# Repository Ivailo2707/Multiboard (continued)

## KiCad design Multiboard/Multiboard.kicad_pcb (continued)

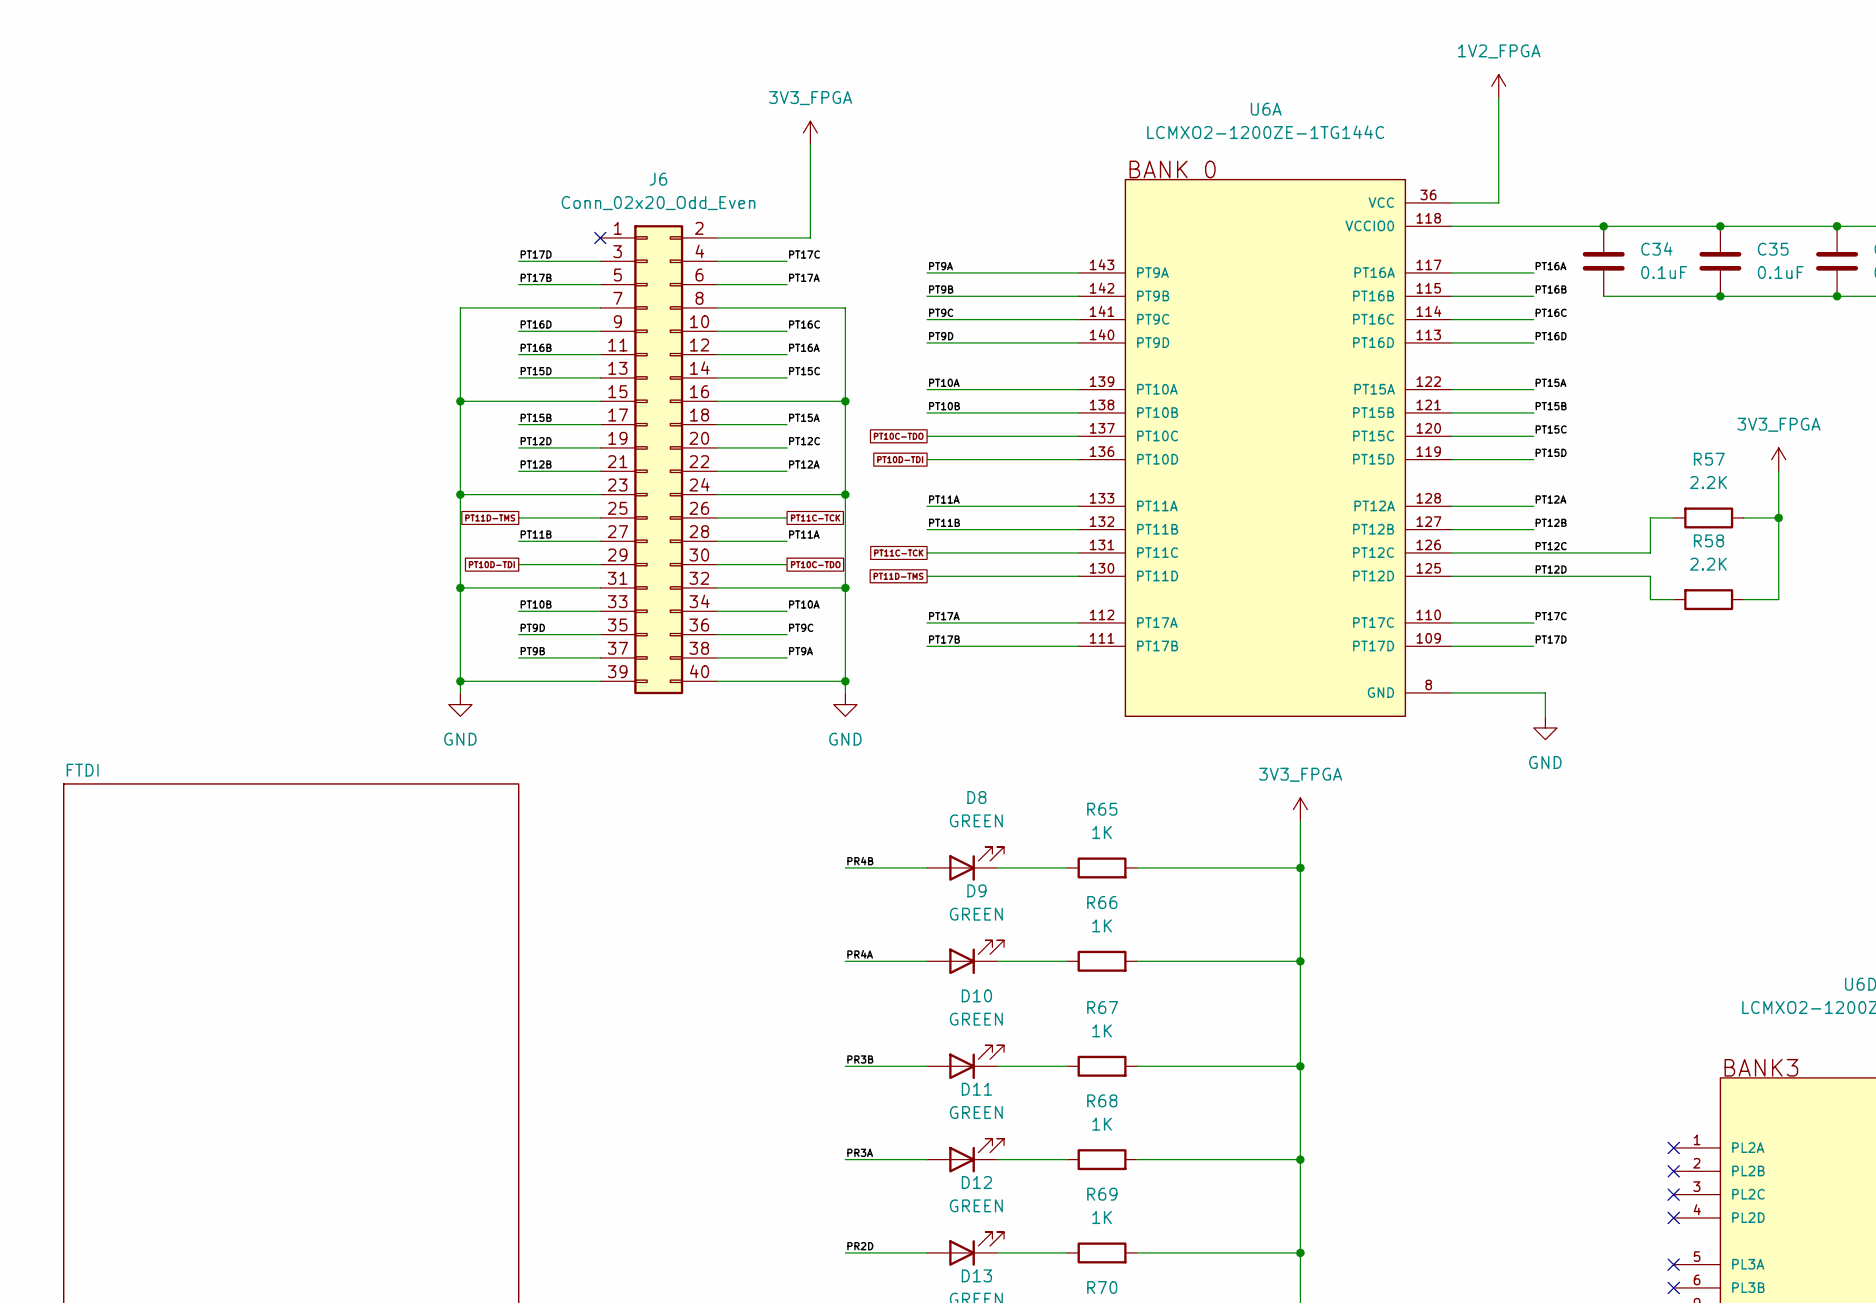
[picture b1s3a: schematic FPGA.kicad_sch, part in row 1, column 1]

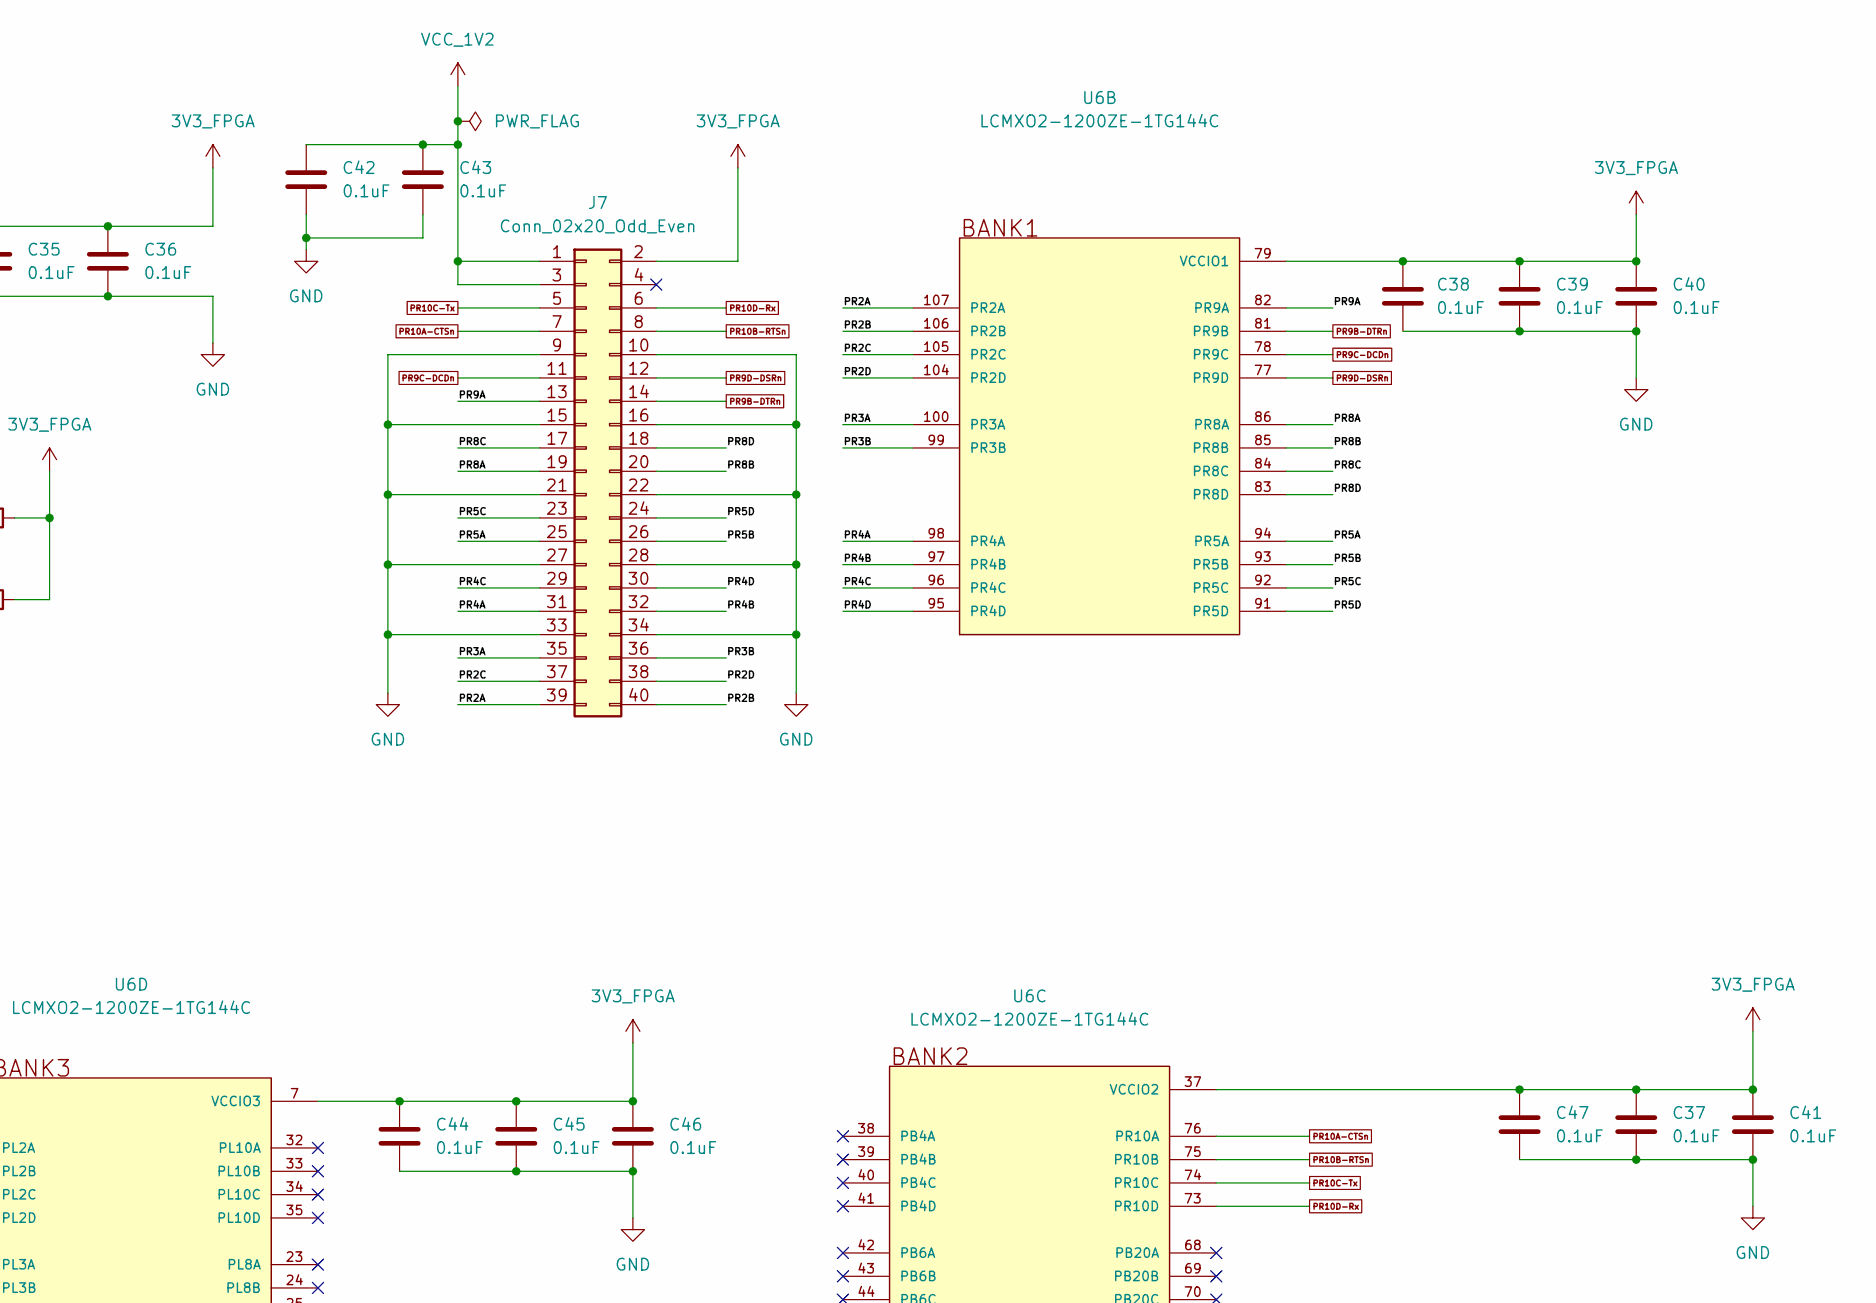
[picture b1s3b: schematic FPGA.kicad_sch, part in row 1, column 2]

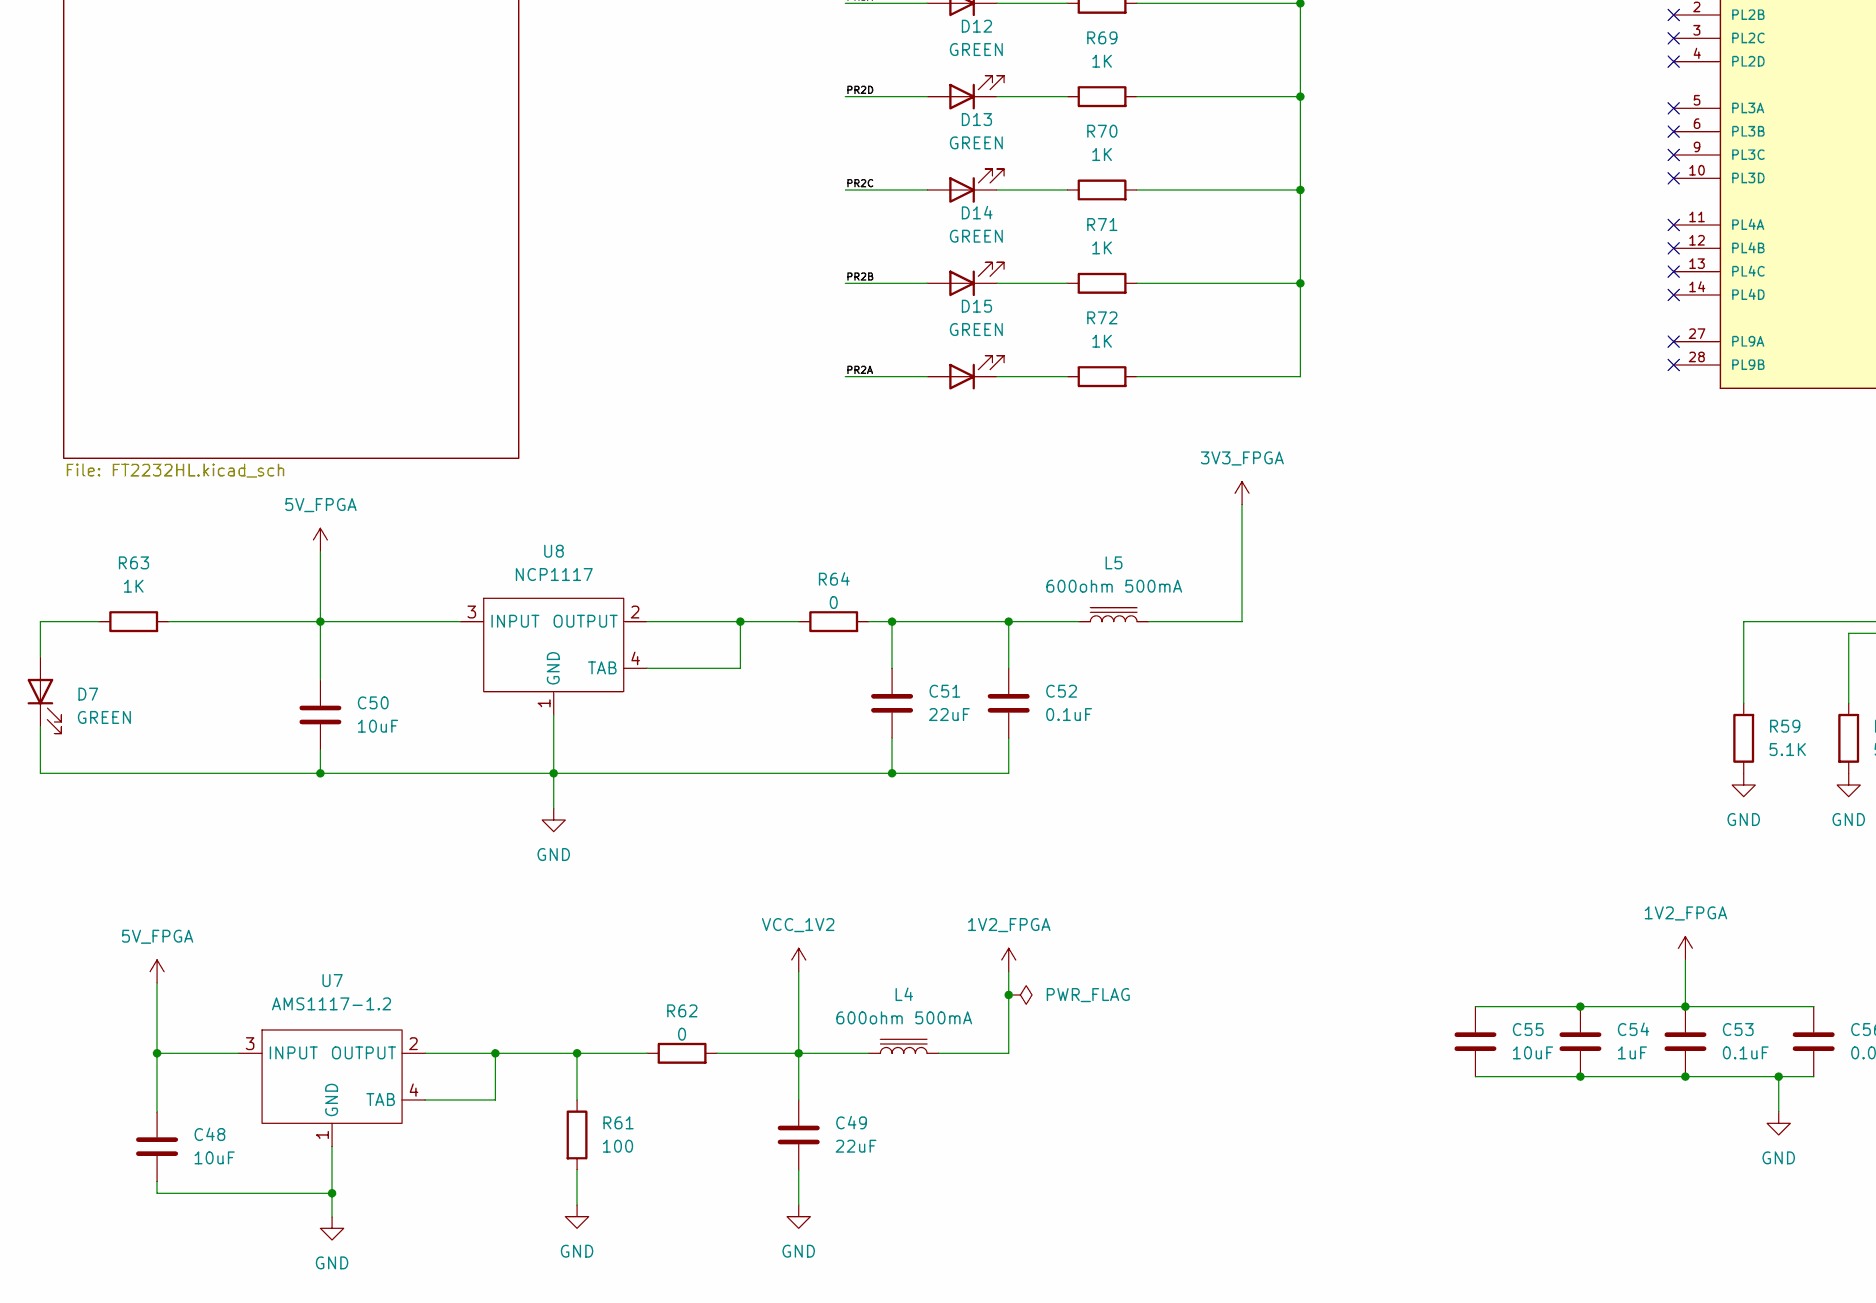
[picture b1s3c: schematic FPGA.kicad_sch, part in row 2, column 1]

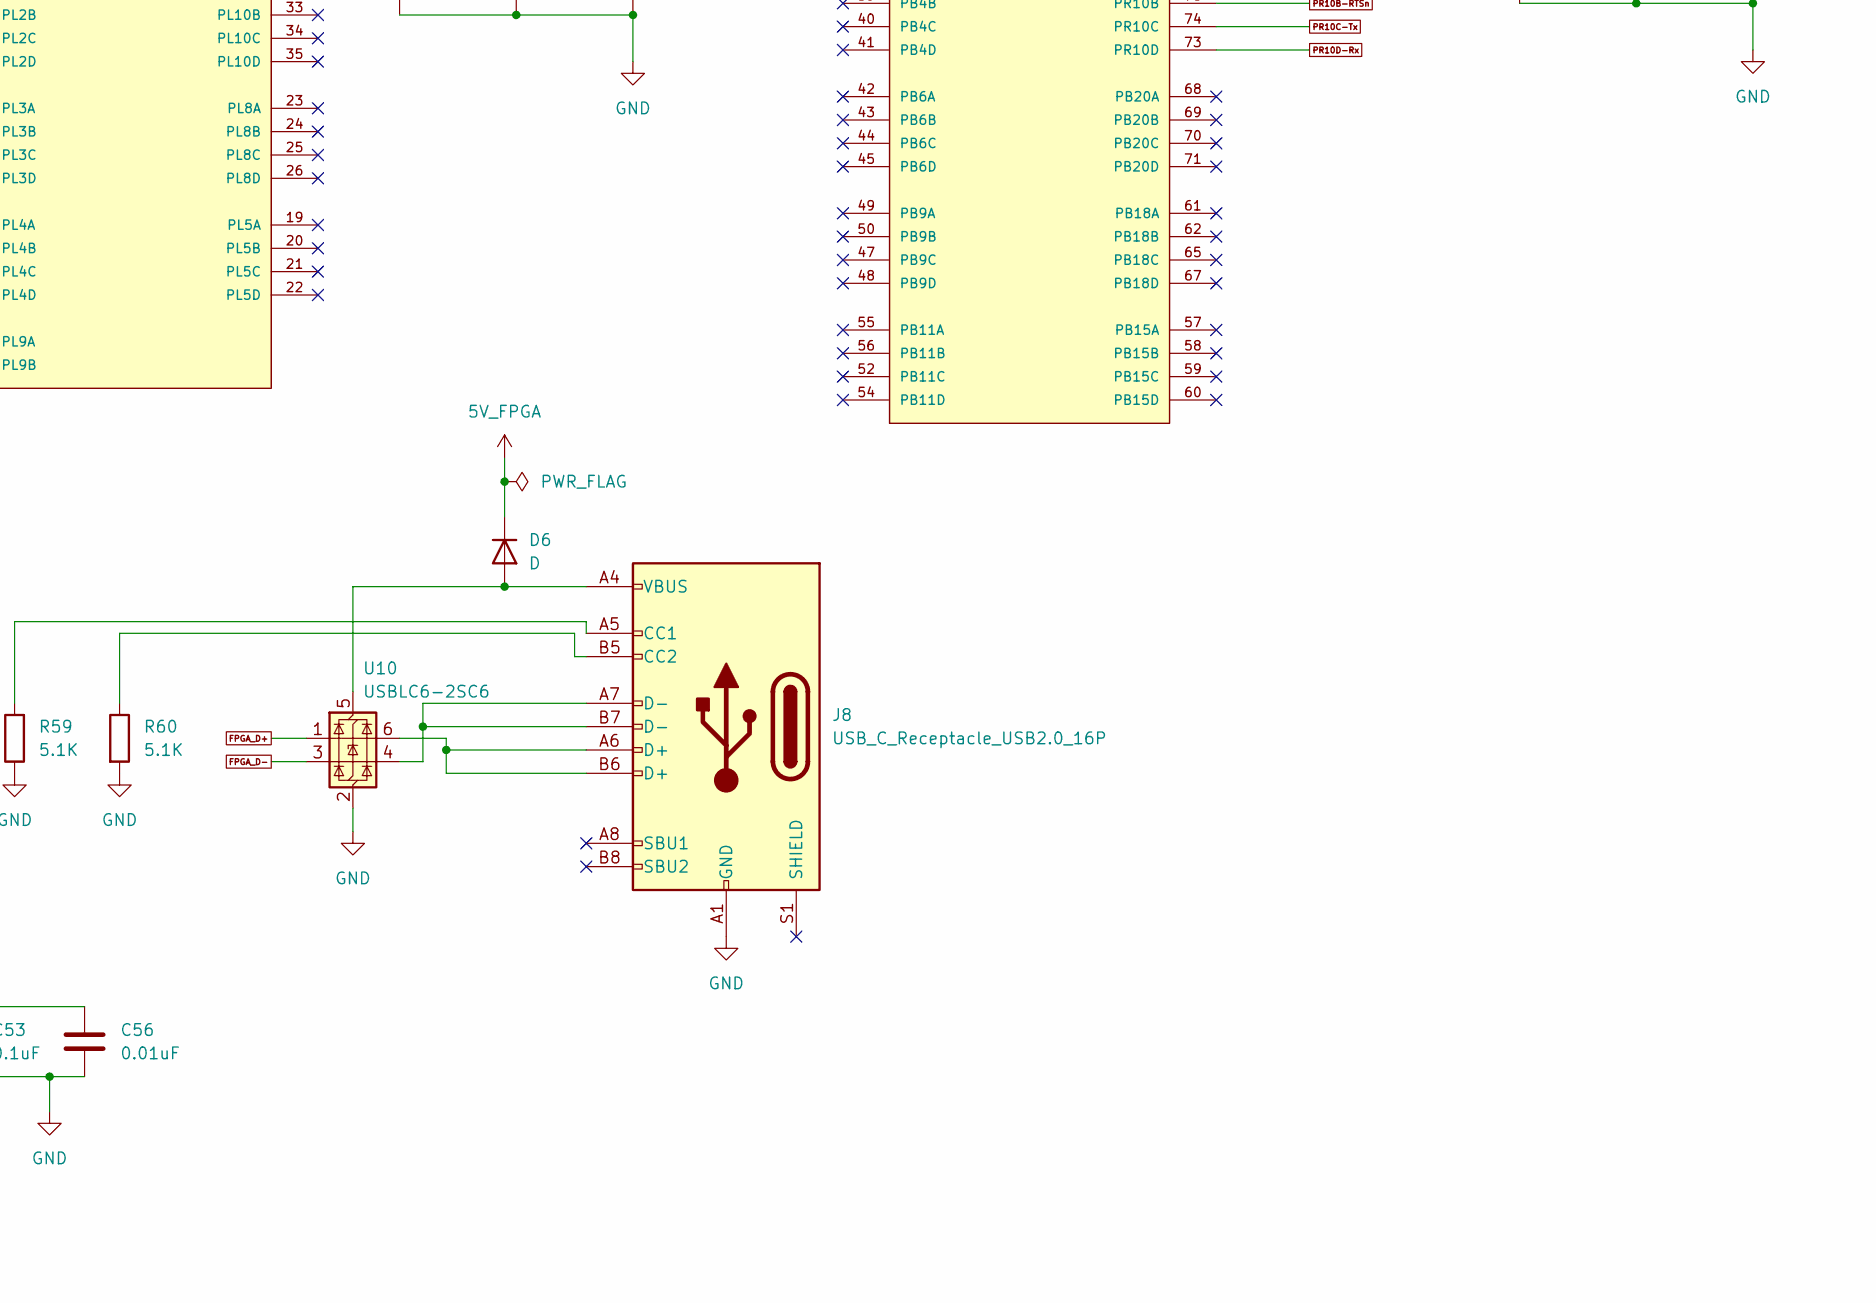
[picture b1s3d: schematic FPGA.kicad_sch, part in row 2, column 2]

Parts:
C34, C35, C36, C37, C38, C39, C40, C41, C42, C43, C44, C45, C46, C47, C52, C53: 0.1uF; C_0603_1608Metric_Pad1.08x0.95mm_HandSolder; LCSC Part Number C14663
C48, C50, C55: 10uF; C_0603_1608Metric_Pad1.08x0.95mm_HandSolder; LCSC Part Number C19702
C49, C51: 22uF; C_0603_1608Metric_Pad1.08x0.95mm_HandSolder; LCSC Part Number C86295
C54: 1uF; C_0603_1608Metric_Pad1.08x0.95mm_HandSolder; LCSC Part Number C95843
C56: 0.01uF; C_0603_1608Metric_Pad1.08x0.95mm_HandSolder; LCSC Part Number C100042
D6: D; D_0603_1608Metric_Pad1.05x0.95mm_HandSolder
D7, D8, D9, D10, D11, D12, D13, D14, D15: GREEN; LED_0603_1608Metric_Pad1.05x0.95mm_HandSolder; LCSC Part Number C2994781
J6, J7: Conn_02x20_Odd_Even; PinHeader_2x20_P2.54mm_Vertical
J8: USB_C_Receptacle_USB2.0_16P; USB_C_Receptacle_G-Switch_GT-USB-7010ASV; LCSC Part Number C2988369
L4, L5: 600ohm 500mA; L_0603_1608Metric_Pad1.05x0.95mm_HandSolder; LCSC Part Number C20345
R57, R58: 2.2K; R_0603_1608Metric_Pad0.98x0.95mm_HandSolder; LCSC Part Number C114662
R59, R60: 5.1K; R_0603_1608Metric_Pad0.98x0.95mm_HandSolder; LCSC Part Number C2907044
R61: 100; R_0603_1608Metric_Pad0.98x0.95mm_HandSolder; LCSC Part Number C105588
R62, R64: 0; R_0603_1608Metric_Pad0.98x0.95mm_HandSolder; LCSC Part Number C95177
R63, R65, R66, R67, R68, R69, R70, R71, R72: 1K; R_0603_1608Metric_Pad0.98x0.95mm_HandSolder; LCSC Part Number C22548
U6: LCMXO2-1200ZE-1TG144C; QFP50P2200X2200X160-144N
U7: AMS1117-1.2; SOT-223; LCSC Part Number C14529
U8: NCP1117; SOT-223; LCSC Part Number C20546
U10: USBLC6-2SC6; SOT-23-6; LCSC Part Number C7519

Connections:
1V2_FPGA: C53.1, C54.1, C55.1, C56.1, L4.2, U6.36 (VCC), U6.72 (VCC), U6.108 (VCC), U6.144 (VCC)
3V3_FPGA: C34.1, C35.1, C36.1, C37.1, C38.1, C39.1, C40.1, C41.1, C44.1, C45.1, C46.1, C47.1, J6.2, J7.2, L5.2, R57.1, R58.1, R65.2, R66.2, R67.2, R68.2, R69.2, R70.2, R71.2, R72.2, U6.7 (VCCIO3), U6.16 (VCCIO3), U6.30 (VCCIO3), U6.37 (VCCIO2), U6.51 (VCCIO2), U6.66 (VCCIO2), U6.79 (VCCIO1), U6.88 (VCCIO1), U6.102 (VCCIO1), U6.118 (VCCIO0), U6.123 (VCCIO0), U6.135 (VCCIO0); also elsewhere on the board
5V_FPGA: C48.1, C50.1, D6.1 (K), R63.2, U7.3 (INPUT), U8.3 (INPUT)
/FPGA/PR2A: D15.2 (A), J7.39, U6.107 (PR2A)
/FPGA/PR2B: D14.2 (A), J7.40, U6.106 (PR2B)
/FPGA/PR2C: D13.2 (A), J7.37, U6.105 (PR2C)
/FPGA/PR2D: D12.2 (A), J7.38, U6.104 (PR2D)
/FPGA/PR3A: D11.2 (A), J7.35, U6.100 (PR3A)
/FPGA/PR3B: D10.2 (A), J7.36, U6.99 (PR3B)
/FPGA/PR4A: D9.2 (A), J7.31, U6.98 (PR4A)
/FPGA/PR4B: D8.2 (A), J7.32, U6.97 (PR4B)
/FPGA/PR4C: J7.29, U6.96 (PR4C)
/FPGA/PR4D: J7.30, U6.95 (PR4D)
/FPGA/PR5A: J7.25, U6.94 (PR5A)
/FPGA/PR5B: J7.26, U6.93 (PR5B)
/FPGA/PR5C: J7.23, U6.92 (PR5C)
/FPGA/PR5D: J7.24, U6.91 (PR5D)
/FPGA/PR8A: J7.19, U6.86 (PR8A)
/FPGA/PR8B: J7.20, U6.85 (PR8B)
/FPGA/PR8C: J7.17, U6.84 (PR8C)
/FPGA/PR8D: J7.18, U6.83 (PR8D)
/FPGA/PR9A: J7.13, U6.82 (PR9A)
/FPGA/PT9A: J6.38, U6.143 (PT9A)
/FPGA/PT9B: J6.37, U6.142 (PT9B)
/FPGA/PT9C: J6.36, U6.141 (PT9C)
/FPGA/PT9D: J6.35, U6.140 (PT9D)
/FPGA/PT10A: J6.34, U6.139 (PT10A)
/FPGA/PT10B: J6.33, U6.138 (PT10B)
/FPGA/PT11A: J6.28, U6.133 (PT11A)
/FPGA/PT11B: J6.27, U6.132 (PT11B)
/FPGA/PT12A: J6.22, U6.128 (PT12A)
/FPGA/PT12B: J6.21, U6.127 (PT12B)
/FPGA/PT12C: J6.20, R57.2, U6.126 (PT12C)
/FPGA/PT12D: J6.19, R58.2, U6.125 (PT12D)
/FPGA/PT15A: J6.18, U6.122 (PT15A)
/FPGA/PT15B: J6.17, U6.121 (PT15B)
/FPGA/PT15C: J6.14, U6.120 (PT15C)
/FPGA/PT15D: J6.13, U6.119 (PT15D)
/FPGA/PT16A: J6.12, U6.117 (PT16A)
/FPGA/PT16B: J6.11, U6.115 (PT16B)
/FPGA/PT16C: J6.10, U6.114 (PT16C)
/FPGA/PT16D: J6.9, U6.113 (PT16D)
/FPGA/PT17A: J6.6, U6.112 (PT17A)
/FPGA/PT17B: J6.5, U6.111 (PT17B)
/FPGA/PT17C: J6.4, U6.110 (PT17C)
/FPGA/PT17D: J6.3, U6.109 (PT17D)
FPGA_D+: U10.1 (I/O1); also elsewhere on the board
FPGA_D-: U10.3 (I/O2); also elsewhere on the board
GND: C34.2, C35.2, C36.2, C37.2, C38.2, C39.2, C40.2, C41.2, C42.2, C43.2, C44.2, C45.2, C46.2, C47.2, C48.2, C49.2, C50.2, C51.2, C52.2, C53.2, C54.2, C55.2, C56.2, D7.1 (K), J6.7, J6.8, J6.15, J6.16, J6.23, J6.24, J6.31, J6.32, J6.39, J6.40, J7.9, J7.10, J7.15, J7.16, J7.21, J7.22, J7.27, J7.28, J7.33, J7.34, J8.A1 (GND), J8.A12 (GND), J8.B1 (GND), J8.B12 (GND), R59.1, R60.2, R61.2, U6.8 (GND), U6.18 (GND), U6.29 (GND), U6.46 (GND), U6.53 (GND), U6.64 (GND), U6.80 (GND), U6.89 (GND), U6.90 (GND), U6.101 (GND), U6.116 (GND), U6.124 (GND), U6.134 (GND), U7.1 (GND), U8.1 (GND), U10.2 (GND); also elsewhere on the board
unnamed: C51.1, C52.1, L5.1, R64.2
unnamed: D6.2 (A), J8.A4 (VBUS), J8.A9 (VBUS), J8.B4 (VBUS), J8.B9 (VBUS), U10.5 (VBUS)
unnamed: D7.2 (A), R63.1
unnamed: D8.1 (K), R65.1
unnamed: D9.1 (K), R66.1
unnamed: D10.1 (K), R67.1
unnamed: D11.1 (K), R68.1
unnamed: D12.1 (K), R69.1
unnamed: D13.1 (K), R70.1
unnamed: D14.1 (K), R71.1
unnamed: D15.1 (K), R72.1
unnamed: J8.A5 (CC1), R59.2
unnamed: J8.B5 (CC2), R60.1
unnamed: J8.A6 (D+), J8.B6 (D+), U10.6 (I/O1)
unnamed: J8.A7 (D-), J8.B7 (D-), U10.4 (I/O2)
unnamed: R61.1, R62.1, U7.2 (OUTPUT), U7.4 (TAB)
unnamed: R64.1, U8.2 (OUTPUT), U8.4 (TAB)
PR9B-DTRn: J7.14, U6.81 (PR9B); also elsewhere on the board
PR9C-DCDn: J7.11, U6.78 (PR9C); also elsewhere on the board
PR9D-DSRn: J7.12, U6.77 (PR9D); also elsewhere on the board
PR10A-CTSn: J7.7, U6.76 (PR10A); also elsewhere on the board
PR10B-RTSn: J7.8, U6.75 (PR10B); also elsewhere on the board
PR10C-Tx: J7.5, U6.74 (PR10C); also elsewhere on the board
PR10D-Rx: J7.6, U6.73 (PR10D); also elsewhere on the board
PT10C-TDO: J6.30, U6.137 (PT10C); also elsewhere on the board
PT10D-TDI: J6.29, U6.136 (PT10D); also elsewhere on the board
PT11C-TCK: J6.26, U6.131 (PT11C); also elsewhere on the board
PT11D-TMS: J6.25, U6.130 (PT11D); also elsewhere on the board
VCC_1V2: C42.1, C43.1, C49.1, J7.1, J7.3, L4.1, R62.2

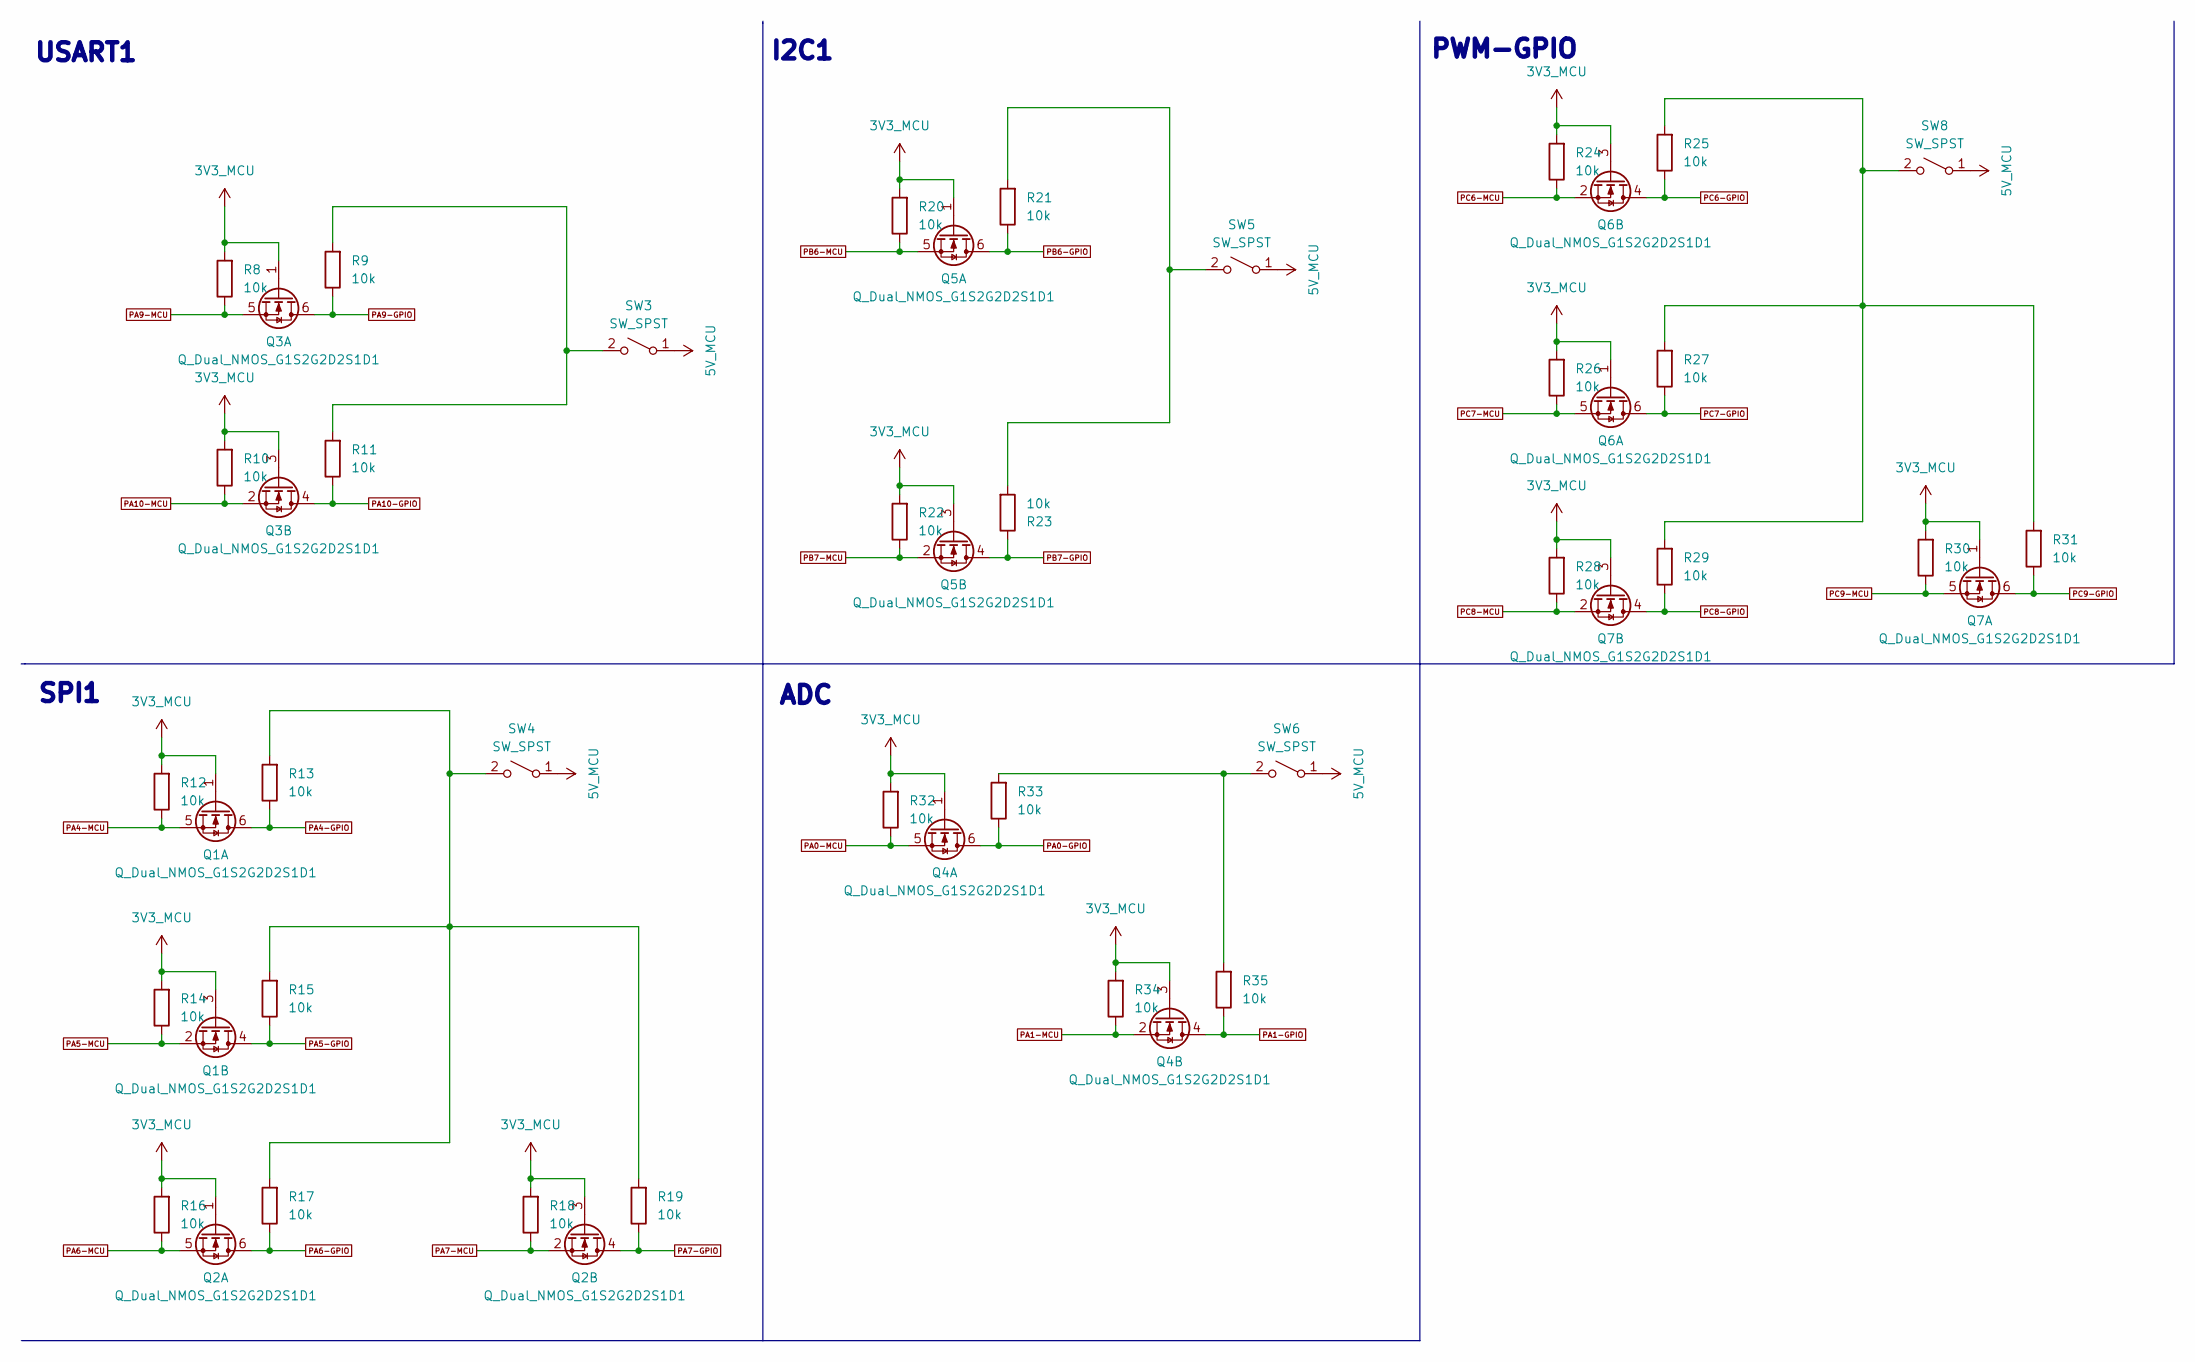
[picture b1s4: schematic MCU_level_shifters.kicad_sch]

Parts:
Q1, Q2, Q3, Q4, Q5, Q6, Q7: Q_Dual_NMOS_G1S2G2D2S1D1; SOT-23-6_Handsoldering; LCSC Part Number C404322
R8, R9, R10, R11, R12, R13, R14, R15, R16, R17, R18, R19, R20, R21, R22, R23, R24, R25, R26, R27, R28, R29, R30, R31, R32, R33, R34, R35: 10k; R_0603_1608Metric_Pad0.98x0.95mm_HandSolder; LCSC Part Number C98220
SW3, SW4, SW5, SW6, SW8: SW_SPST; SW_DIP_SPSTx01_Slide_9.78x4.72mm_W7.62mm_P2.54mm; LCSC Part Number C41381904

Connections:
3V3_MCU: Q1.1 (G), Q1.3 (G), Q2.1 (G), Q2.3 (G), Q3.1 (G), Q3.3 (G), Q4.1 (G), Q4.3 (G), Q5.1 (G), Q5.3 (G), Q6.1 (G), Q6.3 (G), Q7.1 (G), Q7.3 (G), R8.2, R10.2, R12.2, R14.2, R16.2, R18.2, R20.2, R22.2, R24.2, R26.2, R28.2, R30.2, R32.2, R34.2; also elsewhere on the board
5V_MCU: SW3.1 (A), SW4.1 (A), SW5.1 (A), SW6.1 (A), SW8.1 (A); also elsewhere on the board
unnamed: R9.2, R11.2, SW3.2 (B)
unnamed: R13.2, R15.2, R17.2, R19.2, SW4.2 (B)
unnamed: R21.2, R23.2, SW5.2 (B)
unnamed: R33.2, R35.2, SW6.2 (B)
unnamed: R25.2, R27.2, R29.2, R31.2, SW8.2 (B)
PA0-GPIO: Q4.6 (D), R33.1; also elsewhere on the board
PA0-MCU: Q4.5 (S), R32.1; also elsewhere on the board
PA1-GPIO: Q4.4 (D), R35.1; also elsewhere on the board
PA1-MCU: Q4.2 (S), R34.1; also elsewhere on the board
PA4-GPIO: Q1.6 (D), R13.1; also elsewhere on the board
PA4-MCU: Q1.5 (S), R12.1; also elsewhere on the board
PA5-GPIO: Q1.4 (D), R15.1; also elsewhere on the board
PA5-MCU: Q1.2 (S), R14.1; also elsewhere on the board
PA6-GPIO: Q2.6 (D), R17.1; also elsewhere on the board
PA6-MCU: Q2.5 (S), R16.1; also elsewhere on the board
PA7-GPIO: Q2.4 (D), R19.1; also elsewhere on the board
PA7-MCU: Q2.2 (S), R18.1; also elsewhere on the board
PA9-GPIO: Q3.6 (D), R9.1; also elsewhere on the board
PA9-MCU: Q3.5 (S), R8.1; also elsewhere on the board
PA10-GPIO: Q3.4 (D), R11.1; also elsewhere on the board
PA10-MCU: Q3.2 (S), R10.1; also elsewhere on the board
PB6-GPIO: Q5.6 (D), R21.1; also elsewhere on the board
PB6-MCU: Q5.5 (S), R20.1; also elsewhere on the board
PB7-GPIO: Q5.4 (D), R23.1; also elsewhere on the board
PB7-MCU: Q5.2 (S), R22.1; also elsewhere on the board
PC6-GPIO: Q6.4 (D), R25.1; also elsewhere on the board
PC6-MCU: Q6.2 (S), R24.1; also elsewhere on the board
PC7-GPIO: Q6.6 (D), R27.1; also elsewhere on the board
PC7-MCU: Q6.5 (S), R26.1; also elsewhere on the board
PC8-GPIO: Q7.4 (D), R29.1; also elsewhere on the board
PC8-MCU: Q7.2 (S), R28.1; also elsewhere on the board
PC9-GPIO: Q7.6 (D), R31.1; also elsewhere on the board
PC9-MCU: Q7.5 (S), R30.1; also elsewhere on the board

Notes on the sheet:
SPI1
PWM-GPIO
USART1
ADC
I2C1

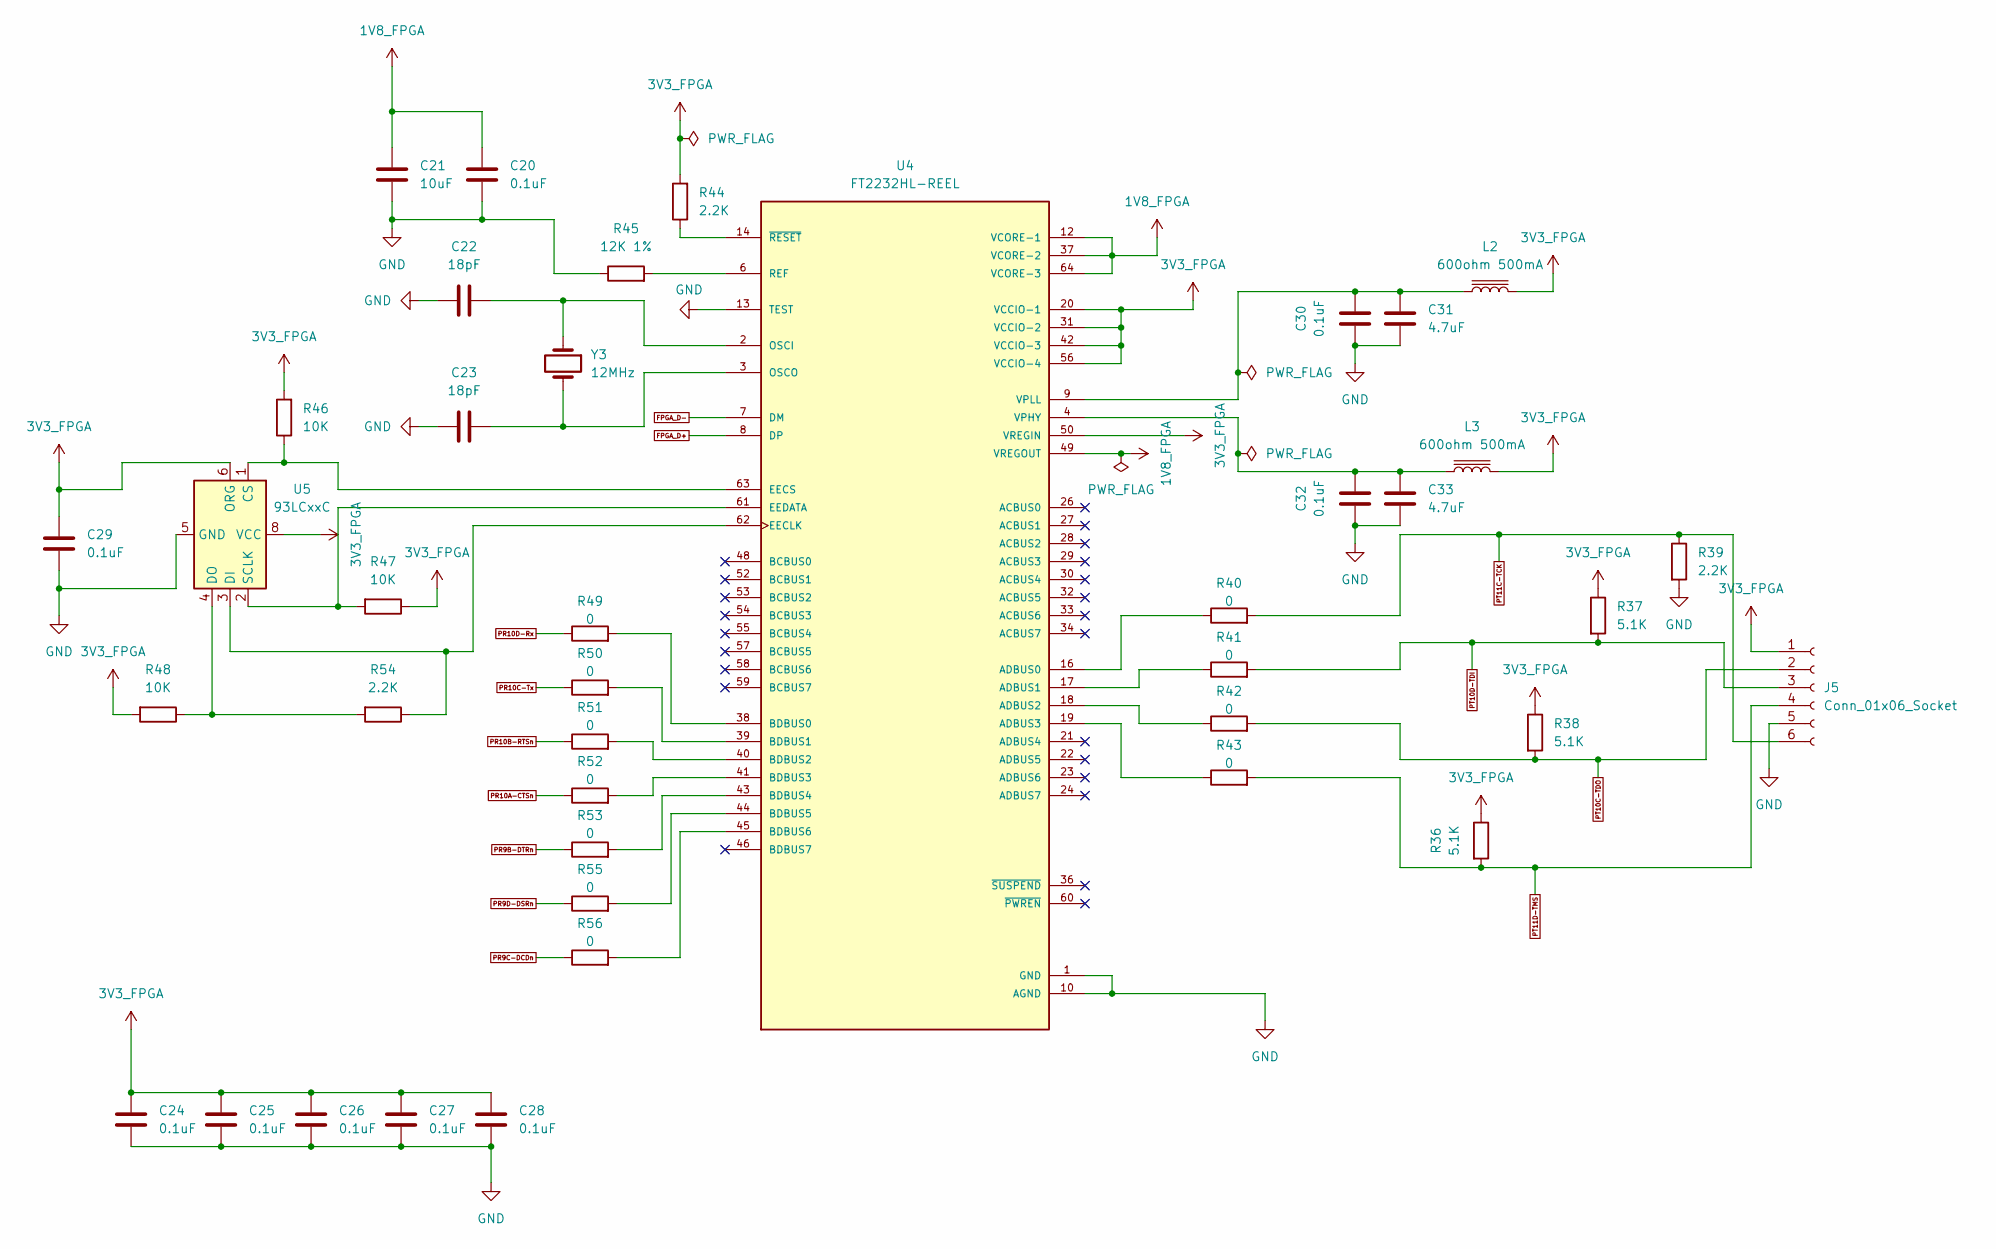
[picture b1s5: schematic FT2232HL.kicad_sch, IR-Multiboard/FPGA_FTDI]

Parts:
C20, C24, C25, C26, C27, C28, C29, C30, C32: 0.1uF; C_0603_1608Metric_Pad1.08x0.95mm_HandSolder; LCSC Part Number C14663
C21: 10uF; C_0603_1608Metric_Pad1.08x0.95mm_HandSolder; LCSC Part Number C19702
C22, C23: 18pF; C_0603_1608Metric_Pad1.08x0.95mm_HandSolder; LCSC Part Number C49326300
C31, C33: 4.7uF; C_0603_1608Metric_Pad1.08x0.95mm_HandSolder; LCSC Part Number C19666
J5: Conn_01x06_Socket; Hirose_DF13-06P-1.25DSA_1x06_P1.25mm_Vertical
L2, L3: 600ohm 500mA; L_0603_1608Metric_Pad1.05x0.95mm_HandSolder; LCSC Part Number C20345
R36, R37, R38: 5.1K; R_0603_1608Metric_Pad0.98x0.95mm_HandSolder; LCSC Part Number C2907044
R39, R44, R54: 2.2K; R_0603_1608Metric_Pad0.98x0.95mm_HandSolder; LCSC Part Number C114662
R40, R41, R42, R43, R49, R50, R51, R52, R53, R55, R56: 0; R_0603_1608Metric_Pad0.98x0.95mm_HandSolder; LCSC Part Number C95177
R45: 12K 1%; R_0603_1608Metric_Pad0.98x0.95mm_HandSolder; LCSC Part Number C431727
R46, R47, R48: 10K; R_0603_1608Metric_Pad0.98x0.95mm_HandSolder; LCSC Part Number C98220
U4: FT2232HL-REEL; QFP50P1200X1200X160-64N; LCSC Part Number C27882
U5: 93LCxxC; SO-8_3.9x4.9mm_P1.27mm; LCSC Part Number C1350395
Y3: 12MHz; Crystal_SMD_TXC_7A-2Pin_5x3.2mm

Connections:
1V8_FPGA: C20.1, C21.1, U4.12 (VCORE-1), U4.37 (VCORE-2), U4.49 (VREGOUT), U4.64 (VCORE-3)
3V3_FPGA: C24.1, C25.1, C26.1, C27.1, C28.1, C29.1, J5.1, L2.2, L3.2, R36.1, R37.1, R38.1, R44.2, R46.2, R47.1, R48.2, U4.20 (VCCIO-1), U4.31 (VCCIO-2), U4.42 (VCCIO-3), U4.50 (VREGIN), U4.56 (VCCIO-4), U5.6 (ORG), U5.8 (VCC); also elsewhere on the board
FPGA_D+: U4.8 (DP); also elsewhere on the board
FPGA_D-: U4.7 (DM); also elsewhere on the board
GND: C20.2, C21.2, C22.1, C23.2, C24.2, C25.2, C26.2, C27.2, C28.2, C29.2, C30.1, C31.1, C32.1, C33.1, J5.5, R39.2, R45.1, U4.1 (GND), U4.5 (GND), U4.10 (AGND), U4.11 (GND), U4.13 (TEST), U4.15 (GND), U4.25 (GND), U4.35 (GND), U4.47 (GND), U4.51 (GND), U5.5 (GND); also elsewhere on the board
unnamed: R40.1, U4.16 (ADBUS0)
unnamed: R41.1, U4.17 (ADBUS1)
unnamed: R42.1, U4.18 (ADBUS2)
unnamed: R43.1, U4.19 (ADBUS3)
unnamed: R49.2, U4.38 (BDBUS0)
unnamed: R50.2, U4.39 (BDBUS1)
unnamed: R51.2, U4.40 (BDBUS2)
unnamed: R52.2, U4.41 (BDBUS3)
unnamed: R53.2, U4.43 (BDBUS4)
unnamed: R55.2, U4.44 (BDBUS5)
unnamed: R56.2, U4.45 (BDBUS6)
unnamed: R54.1, U4.62 (EECLK), U5.3 (DI)
unnamed: R46.1, U4.63 (EECS), U5.1 (CS)
unnamed: R47.2, U4.61 (EEDATA), U5.2 (SCLK)
unnamed: C22.2, U4.2 (OSCI), Y3.1
unnamed: C23.1, U4.3 (OSCO), Y3.2
unnamed: R45.2, U4.6 (REF)
unnamed: C32.2, C33.2, L3.1, U4.4 (VPHY)
unnamed: C30.2, C31.2, L2.1, U4.9 (VPLL)
unnamed: R44.1, U4.14 (~RESET)
unnamed: R48.1, R54.2, U5.4 (DO)
PR9B-DTRn: R53.1; also elsewhere on the board
PR9C-DCDn: R56.1; also elsewhere on the board
PR9D-DSRn: R55.1; also elsewhere on the board
PR10A-CTSn: R52.1; also elsewhere on the board
PR10B-RTSn: R51.1; also elsewhere on the board
PR10C-Tx: R50.1; also elsewhere on the board
PR10D-Rx: R49.1; also elsewhere on the board
PT10C-TDO: J5.2, R38.2, R42.2; also elsewhere on the board
PT10D-TDI: J5.3, R37.2, R41.2; also elsewhere on the board
PT11C-TCK: J5.6, R39.1, R40.2; also elsewhere on the board
PT11D-TMS: J5.4, R36.2, R43.2; also elsewhere on the board

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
